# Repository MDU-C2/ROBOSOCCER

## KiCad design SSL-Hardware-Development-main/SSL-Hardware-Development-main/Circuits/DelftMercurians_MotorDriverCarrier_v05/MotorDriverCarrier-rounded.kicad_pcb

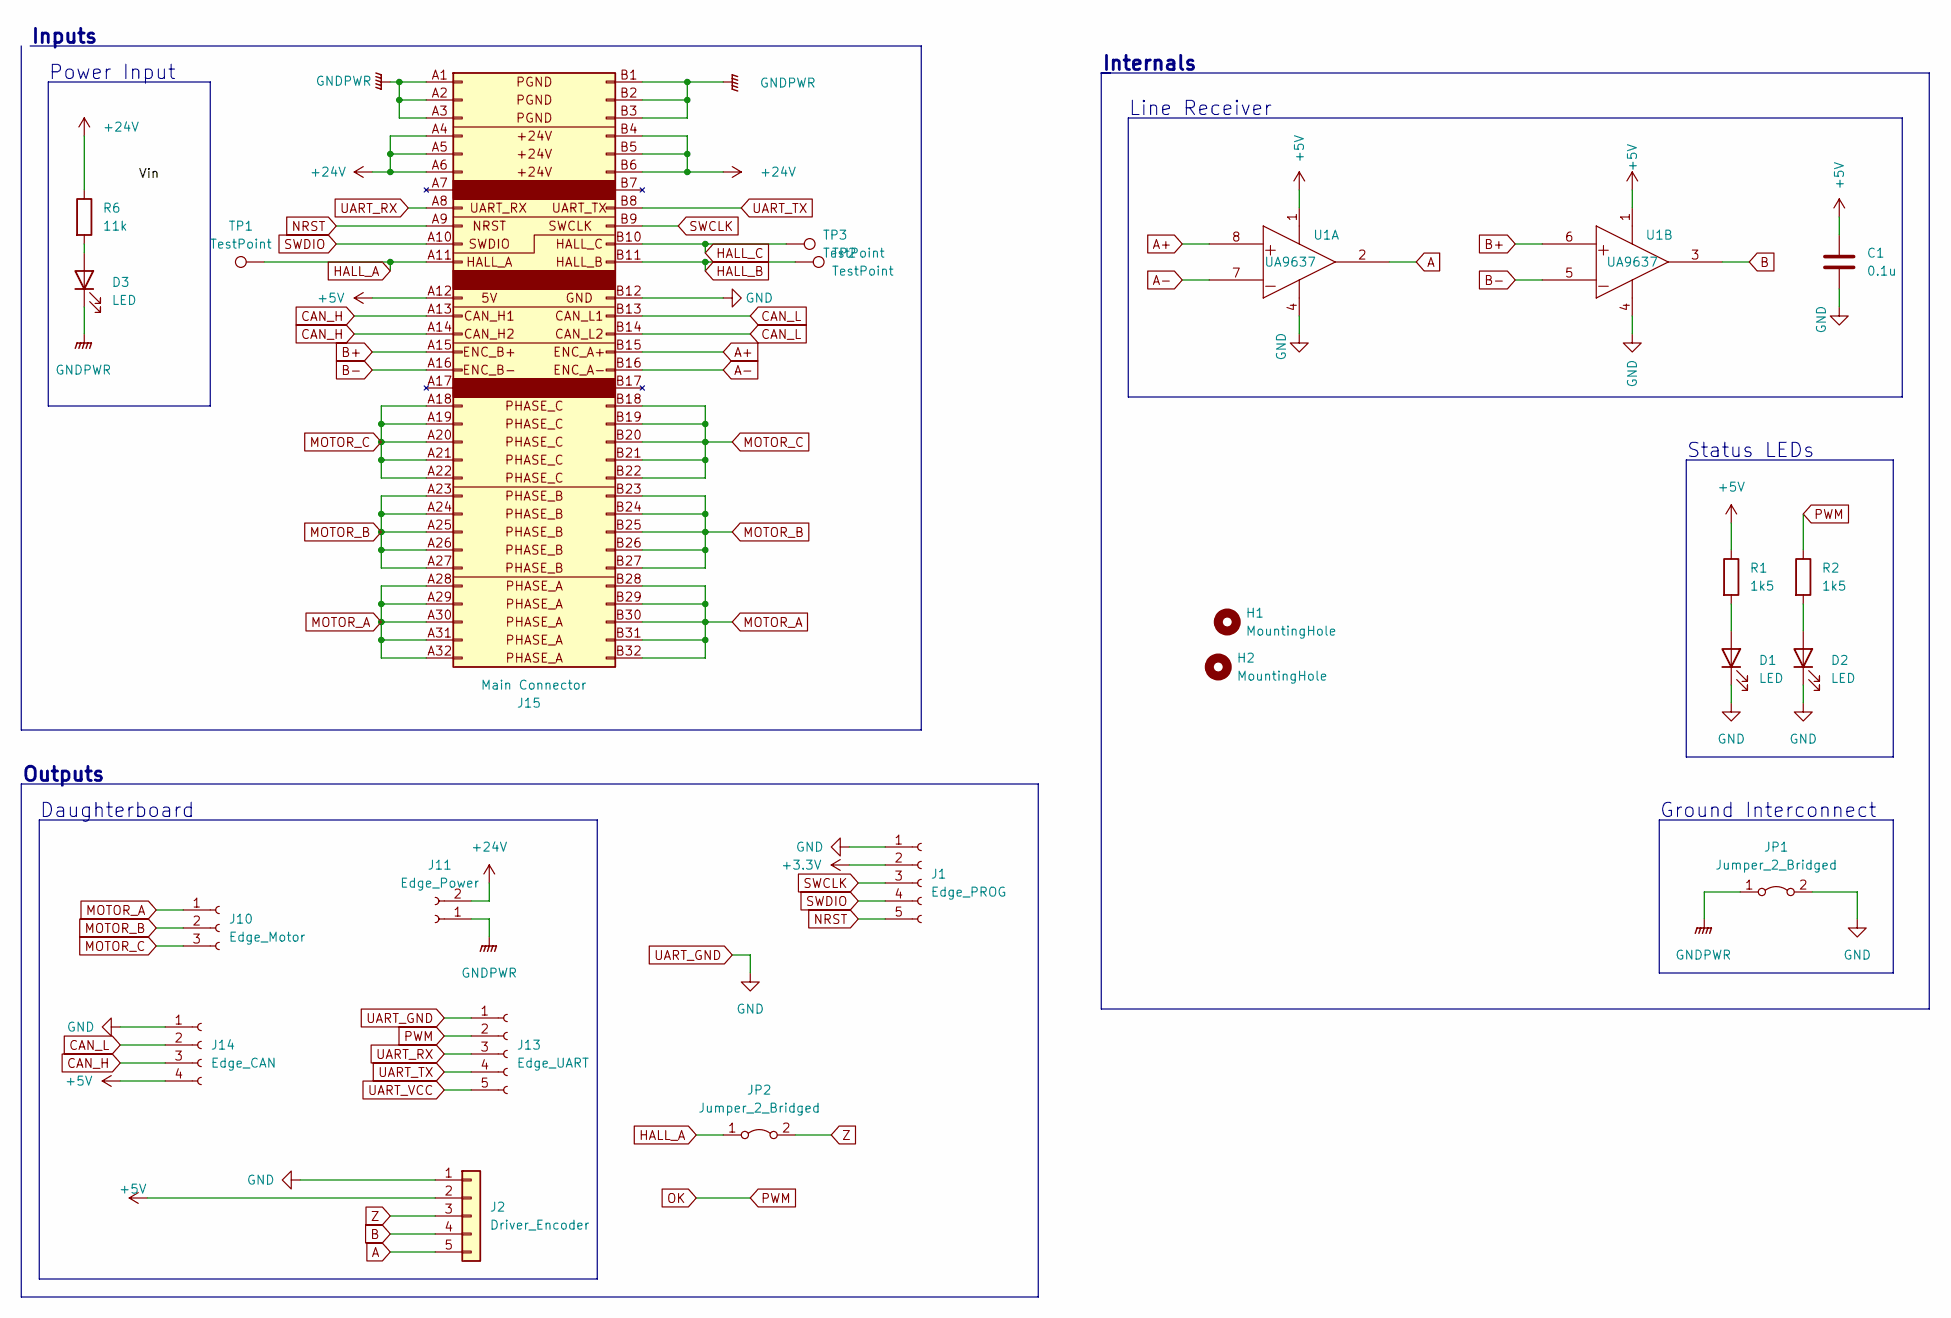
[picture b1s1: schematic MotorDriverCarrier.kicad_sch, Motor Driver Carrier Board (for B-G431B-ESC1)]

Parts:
C1: 0.1u; C_0603_1608Metric_Pad1.08x0.95mm_HandSolder
D1, D2, D3: LED; LED_0603_1608Metric_Pad1.05x0.95mm_HandSolder
H1, H2: MountingHole; MountingHole_3.2mm_M3_ISO14580
J1: Edge_PROG; CustomEdge_PROG
J2: Driver_Encoder; PinHeader_1x05_P2.00mm_Vertical
J10: Edge_Motor; CustomEdge_Motor3_Single
J11: Edge_Power; CustomEdge_Power2
J13: Edge_UART; CustomEdge_UART5
J14: Edge_CAN; CustomEdge_CAN4
J15: Main Connector; BUS_PCIexpress_x4
JP1: Jumper_2_Bridged; SolderJumper-2_P1.3mm_Open_TrianglePad1.0x1.5mm
JP2: Jumper_2_Bridged; SolderJumper-2_P1.3mm_Bridged_RoundedPad1.0x1.5mm
R1, R2: 1k5; R_0603_1608Metric_Pad0.98x0.95mm_HandSolder
R6: 11k; R_0603_1608Metric_Pad0.98x0.95mm_HandSolder
TP1, TP2, TP3: TestPoint; TestPoint_Pad_D1.0mm
U1: UA9637; SOIC-8_3.9x4.9mm_P1.27mm

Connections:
+3.3V: J1.2
+5V: C1.1, J2.2, J14.4, J15.A12 (+5V), R1.1, U1.1 (VCC)
+24V: J11.2, J15.A4 (VCC), J15.A5 (VCC), J15.A6 (VCC), J15.B4 (VCC), J15.B5 (VCC), J15.B6 (VCC), R6.1
A: J2.5, U1.2 (OUT)
A+: J15.B15 (ENC_A+), U1.8 (IN+)
A-: J15.B16 (ENC_A-), U1.7 (IN-)
B: J2.4, U1.3 (OUT)
B+: J15.A15 (ENC_B+), U1.6 (IN+)
B-: J15.A16 (ENC_B-), U1.5 (IN-)
CAN_H: J14.3, J15.A13 (CAN_H), J15.A14 (CAN_H)
CAN_L: J14.2, J15.B13 (CAN_L), J15.B14 (CAN_L)
GNDPWR: D3.1 (K), J11.1, J15.A1 (PGND), J15.A2 (PGND), J15.A3 (PGND), J15.B1 (PGND), J15.B2 (PGND), J15.B3 (PGND), JP1.1 (A)
HALL_A: J15.A11 (HALL_A), JP2.1 (A), TP1.1
HALL_B: J15.B11 (HALL_B), TP2.1
HALL_C: J15.B10 (HALL_C), TP3.1
MOTOR_A: J10.1, J15.A28 (PHASE_A), J15.A29 (PHASE_A), J15.A30 (PHASE_A), J15.A31 (PHASE_A), J15.A32 (PHASE_A), J15.B28 (PHASE_A), J15.B29 (PHASE_A), J15.B30 (PHASE_A), J15.B31 (PHASE_A), J15.B32 (PHASE_A)
MOTOR_B: J10.2, J15.A23 (PHASE_B), J15.A24 (PHASE_B), J15.A25 (PHASE_B), J15.A26 (PHASE_B), J15.A27 (PHASE_B), J15.B23 (PHASE_B), J15.B24 (PHASE_B), J15.B25 (PHASE_B), J15.B26 (PHASE_B), J15.B27 (PHASE_B)
MOTOR_C: J10.3, J15.A18 (PHASE_C), J15.A19 (PHASE_C), J15.A20 (PHASE_C), J15.A21 (PHASE_C), J15.A22 (PHASE_C), J15.B18 (PHASE_C), J15.B19 (PHASE_C), J15.B20 (PHASE_C), J15.B21 (PHASE_C), J15.B22 (PHASE_C)
NRST: J1.5, J15.A9 (NRST)
unnamed: D1.2 (A), R1.2
unnamed: D2.2 (A), R2.2
unnamed: D3.2 (A), R6.2
OK: J13.2, R2.1
SWCLK: J1.3, J15.B9 (SWCLK)
SWDIO: J1.4, J15.A10 (SWDIO)
UART_GND: C1.2, D1.1 (K), D2.1 (K), J1.1, J2.1, J13.1, J14.1, J15.B12 (GND), JP1.2 (B), U1.4 (GND)
UART_RX: J13.3, J15.A8 (UART_RX)
UART_TX: J13.4, J15.B8 (UART_TX)
UART_VCC: J13.5
Z: J2.3, JP2.2 (B)

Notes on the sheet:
Daughterboard
Internals
Status LEDs
Line Receiver
Ground Interconnect
Power Input
Outputs
Inputs

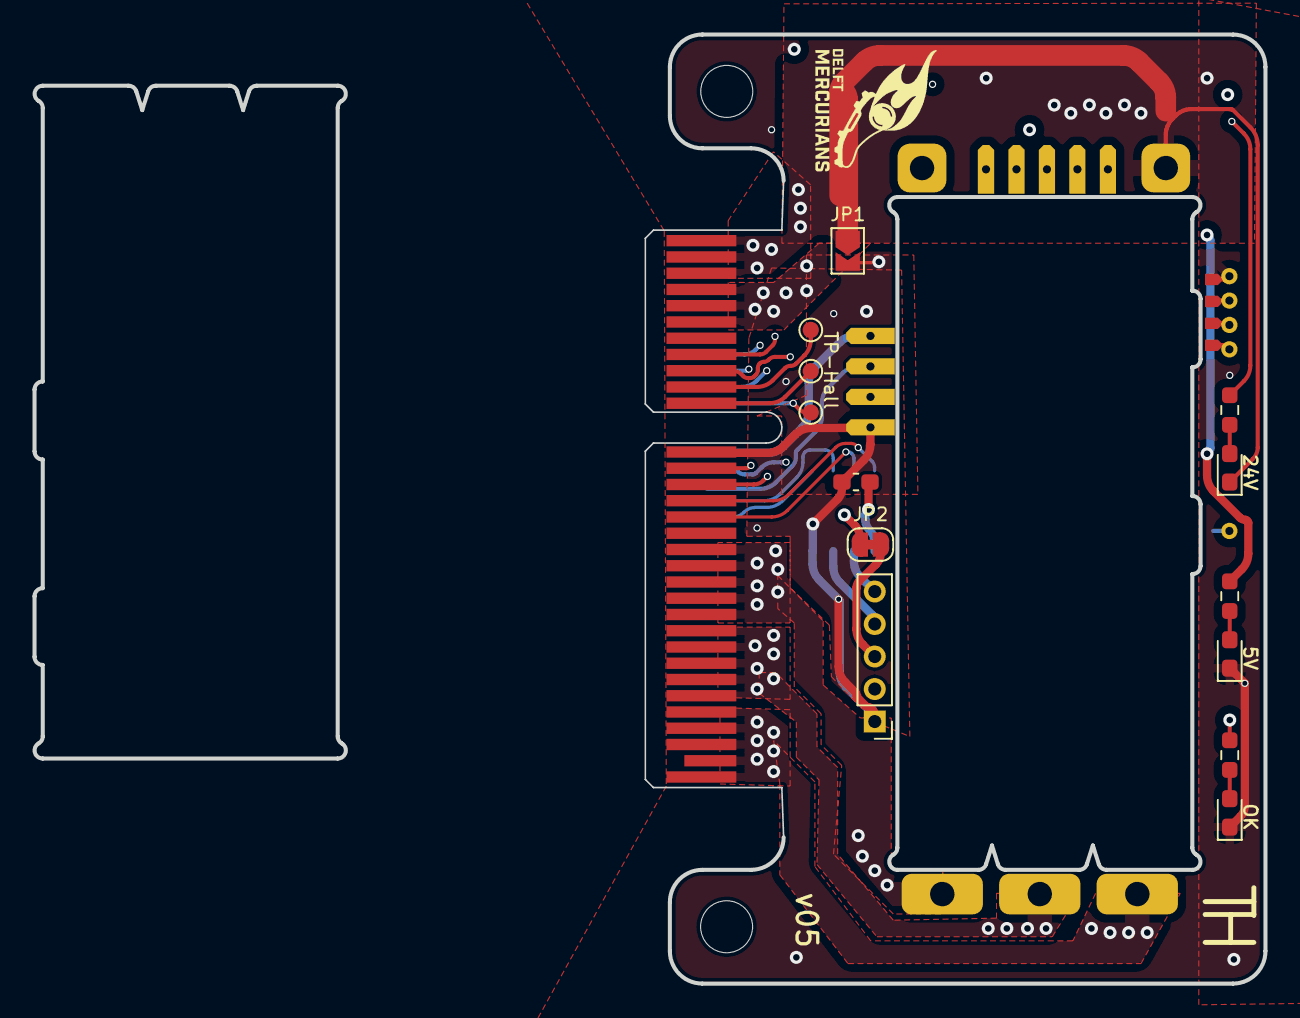
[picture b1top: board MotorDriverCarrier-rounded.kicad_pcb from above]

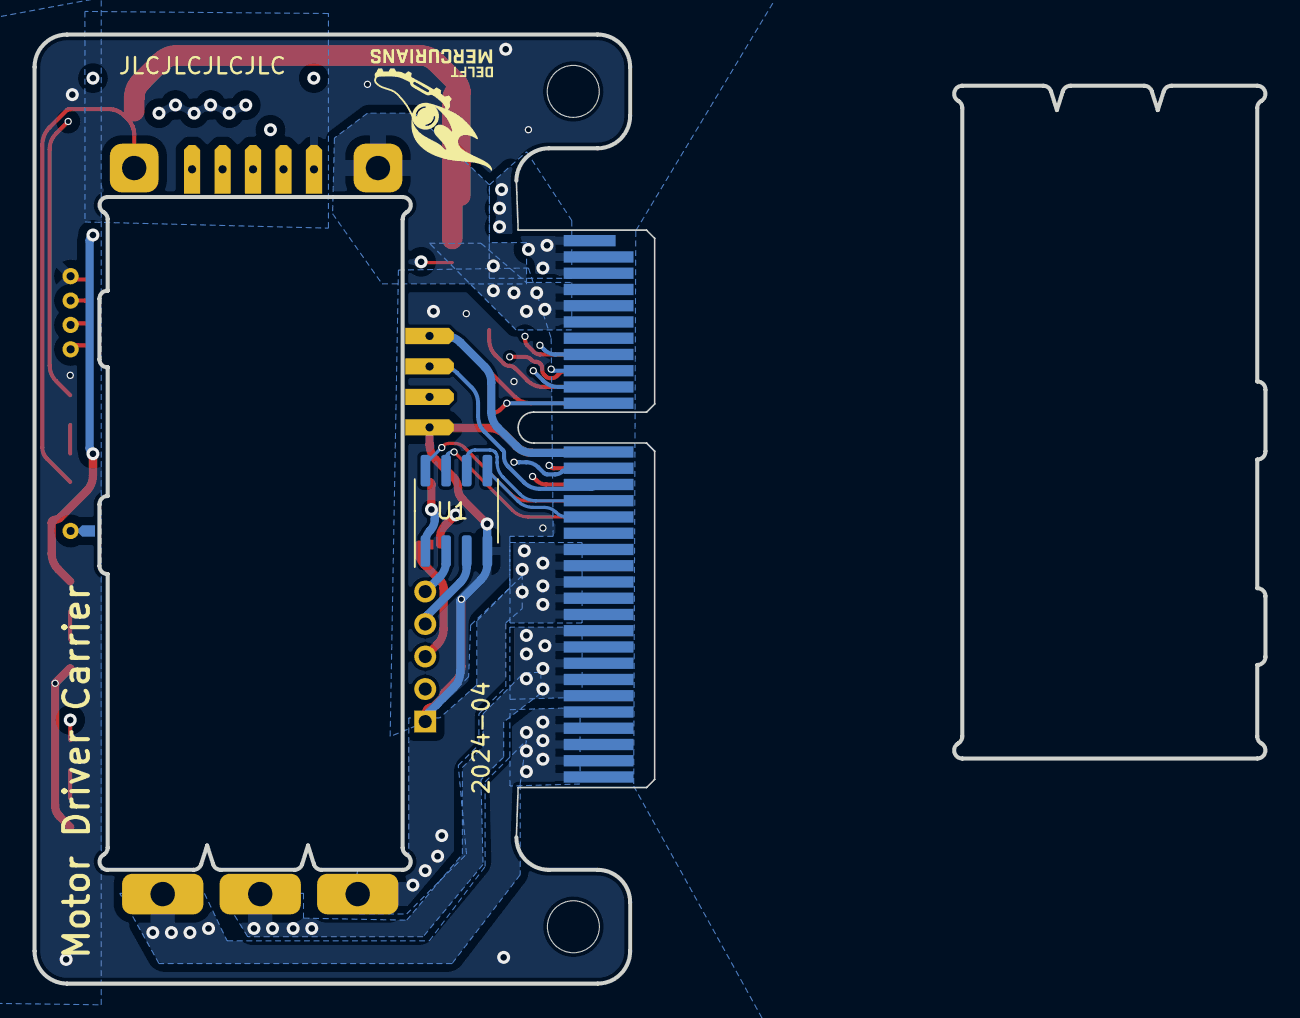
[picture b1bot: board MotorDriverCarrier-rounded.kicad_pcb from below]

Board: 4 copper layers, 38.2 x 58.4 mm, 22 parts (2 on the bottom side), 28 nets.

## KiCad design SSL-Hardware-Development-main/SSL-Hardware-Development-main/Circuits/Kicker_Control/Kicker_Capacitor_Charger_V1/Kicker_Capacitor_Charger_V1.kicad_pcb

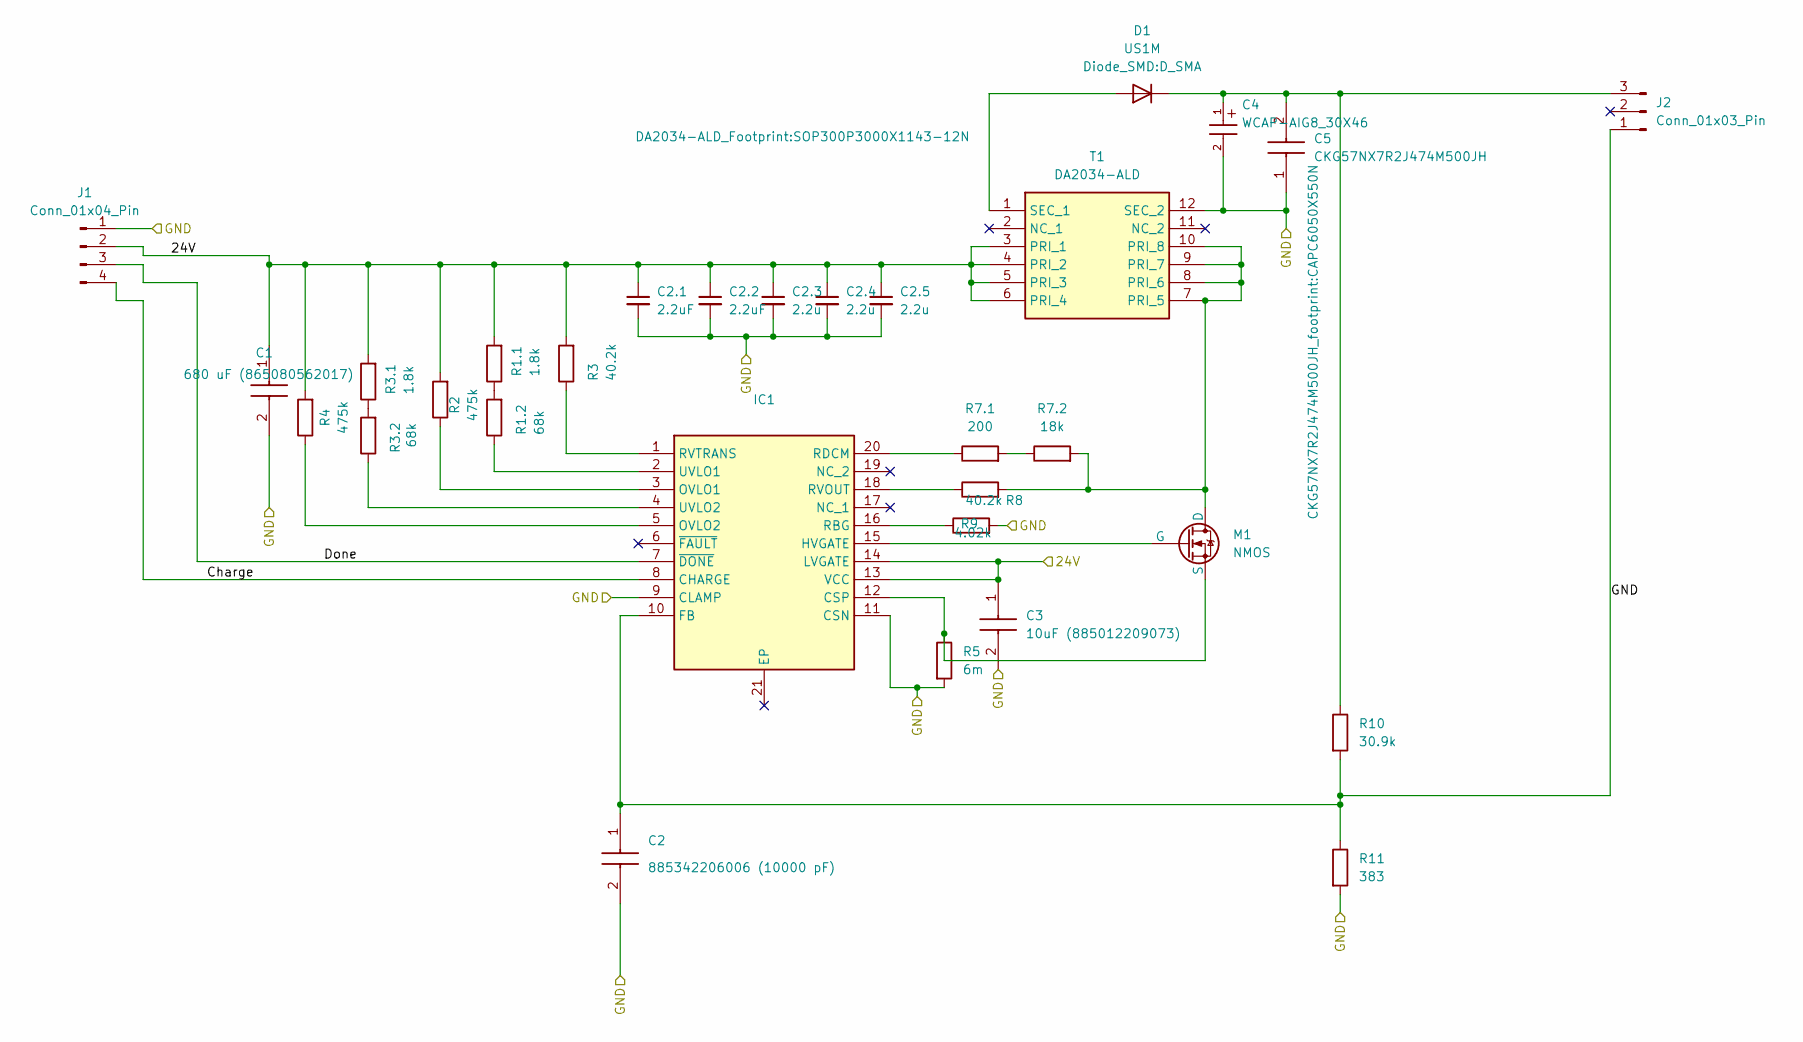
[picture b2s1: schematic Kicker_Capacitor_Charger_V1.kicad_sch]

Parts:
C1: 680 uF (865080562017); CAPAE1350X1400N; Mouser Part Number 710-865080562017
C2: 885342206006 (10000 pF); CAPC1608X87N; Mouser Part Number 710-885342206006
C2.1, C2.2: 2.2uF; C_1210_3225Metric
C2.3, C2.4, C2.5: 2.2u; C_1210_3225Metric
C3: 10uF (885012209073); C_1210_3225Metric; Mouser Part Number 710-885012209073
C4: WCAP-AIG8_30X46; WCAP-AIG8_30X46_DXL_
C5: CKG57NX7R2J474M500JH; CAPC6050X550N; Manufacturer_Part_Number CKG57NX7R2J474M500JH
D1: US1M; D_SMA
IC1: LT3751IFE#PBF; SOP65P640X120-21N; Mouser Part Number 584-LT3751IFE#PBF
J1: Conn_01x04_Pin; PinHeader_1x04_P2.54mm_Vertical
J2: Conn_01x03_Pin; PinHeader_1x03_P2.54mm_Vertical
M1: NMOS; TO-263-3_TabPin2
R1.1, R3.1: 1.8k; R_0603_1608Metric
R1.2, R3.2: 68k; R_1206_3216Metric
R2, R4: 475k; R_0603_1608Metric
R3, R8: 40.2k; R_0603_1608Metric
R5: 6m; R_0805_2012Metric
R7.1: 200; R_0805_2012Metric
R7.2: 18k; R_0603_1608Metric
R9: 4.02k; R_0603_1608Metric
R10: 30.9k; R_1206_3216Metric
R11: 383; R_1206_3216Metric
T1: DA2034-ALD; SOP300P3000X1143-12N; Mouser Part Number 994-DA2034-ALD

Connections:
/24V: C1.1 (+), C2.1.1, C2.2.1, C2.3.1, C2.4.1, C2.5.1, C3.1, IC1.13 (VCC), IC1.14 (LVGATE), J1.2, R1.1.2, R2.2, R3.2, R3.1.2, R4.2, T1.3 (PRI_1), T1.4 (PRI_2), T1.5 (PRI_3), T1.6 (PRI_4)
/Charge: IC1.8 (CHARGE), J1.4
/Done: IC1.7 (~DONE), J1.3
/GND: C1.2 (-), C2.1, C2.2, C2.1.2, C2.2.2, C2.3.2, C2.4.2, C2.5.2, C3.2, C4.2, C5.1, IC1.9 (CLAMP), IC1.10 (FB), IC1.11 (CSN), J1.1, J2.1, R5.2, R9.2, R10.2, R11.1, R11.2, T1.12 (SEC_2)
unnamed: D1.2 (A), T1.1 (SEC_1)
unnamed: C4.1, C5.2, D1.1 (K), J2.3, R10.1
unnamed: IC1.12 (CSP), M1.3 (S), R5.1
unnamed: IC1.15 (HVGATE), M1.2 (G)
unnamed: IC1.3 (OVLO1), R2.1
unnamed: IC1.5 (OVLO2), R4.1
unnamed: IC1.16 (RBG), R9.1
unnamed: IC1.20 (RDCM), R7.1.1
unnamed: IC1.18 (RVOUT), R8.1
unnamed: IC1.1 (RVTRANS), R3.1
unnamed: IC1.2 (UVLO1), R1.2.1
unnamed: IC1.4 (UVLO2), R3.2.1
unnamed: M1.1 (D), R7.2.2, R8.2, T1.7 (PRI_5), T1.8 (PRI_6), T1.9 (PRI_7), T1.10 (PRI_8)
unnamed: R1.1.1, R1.2.2
unnamed: R3.1.1, R3.2.2
unnamed: R7.1.2, R7.2.1

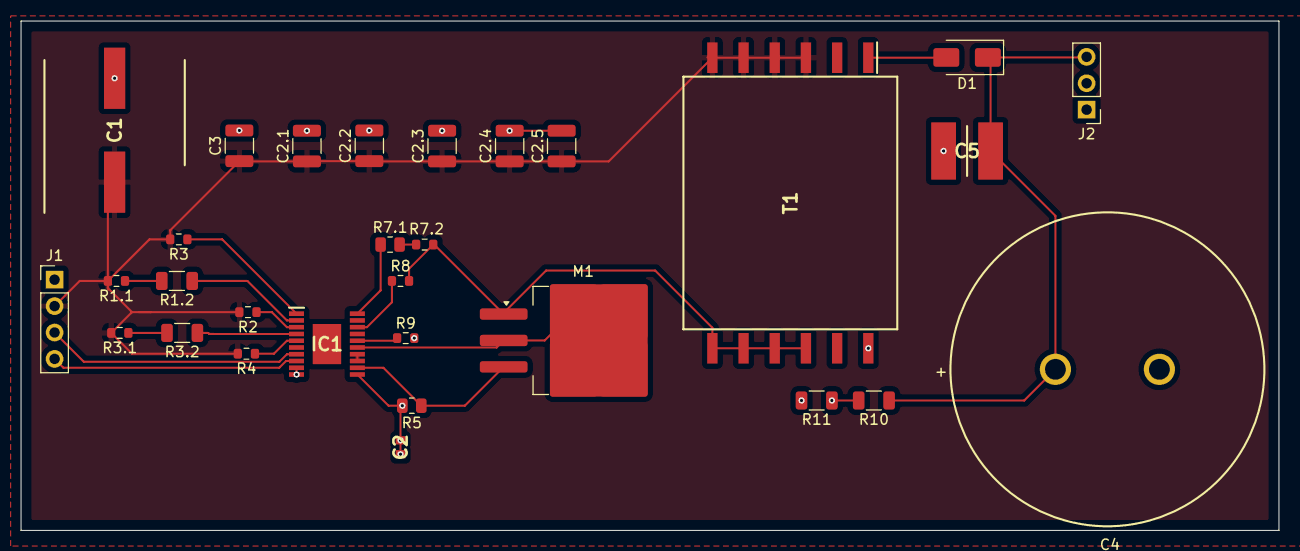
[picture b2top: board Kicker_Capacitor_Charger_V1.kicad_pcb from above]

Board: 2 copper layers, 121.0 x 49.0 mm, 30 parts (0 on the bottom side), 20 nets.
